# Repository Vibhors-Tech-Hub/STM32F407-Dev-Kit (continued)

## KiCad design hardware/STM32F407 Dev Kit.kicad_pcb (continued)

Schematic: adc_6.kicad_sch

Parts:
C28, C29, C30: 100n; C_0805_2012Metric_Pad1.18x1.45mm_HandSolder
C31, C32, C33: 10n; C_0805_2012Metric_Pad1.18x1.45mm_HandSolder
FB2: ILHB0805ER102VHC41; C_0805_2012Metric_Pad1.18x1.45mm_HandSolder
J5: Conn_01x04; PinHeader_1x04_P2.54mm_Vertical
R17: 10K; R_0805_2012Metric_Pad1.20x1.40mm_HandSolder
R18, R19: 1K; R_0805_2012Metric_Pad1.20x1.40mm_HandSolder
U5: ADS122C04IPW; TSSOP-16_4.4x5mm_P0.65mm

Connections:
+3V3: C28.1, C33.1, FB2.2, J5.1, R17.1, U5.13 (DVDD); also elsewhere on the board
/[6] - ADC/AIN1: C30.2, C31.1, R19.1, U5.10 (AIN1)
/[6] - ADC/AIN2: C30.1, C32.1, R18.1, U5.7 (AIN2)
/[6] - ADC/SENSOR_PIN1: J5.3, R19.2
/[6] - ADC/SENSOR_PIN2: J5.2, R18.2
ADC_DRDY: U5.14 (DRDY); also elsewhere on the board
ADC_RST: R17.2, U5.3 (RESET); also elsewhere on the board
GND: C28.2, C29.2, C31.2, C32.2, C33.2, J5.4, U5.1 (A0), U5.2 (A1), U5.4 (DGND), U5.5 (AVSS); also elsewhere on the board
unnamed: C29.1, FB2.1, U5.12 (AVDD)
SCL: U5.16 (SCL); also elsewhere on the board
SDA: U5.15 (SDA); also elsewhere on the board

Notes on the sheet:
ADC
Address: 100000
Connector

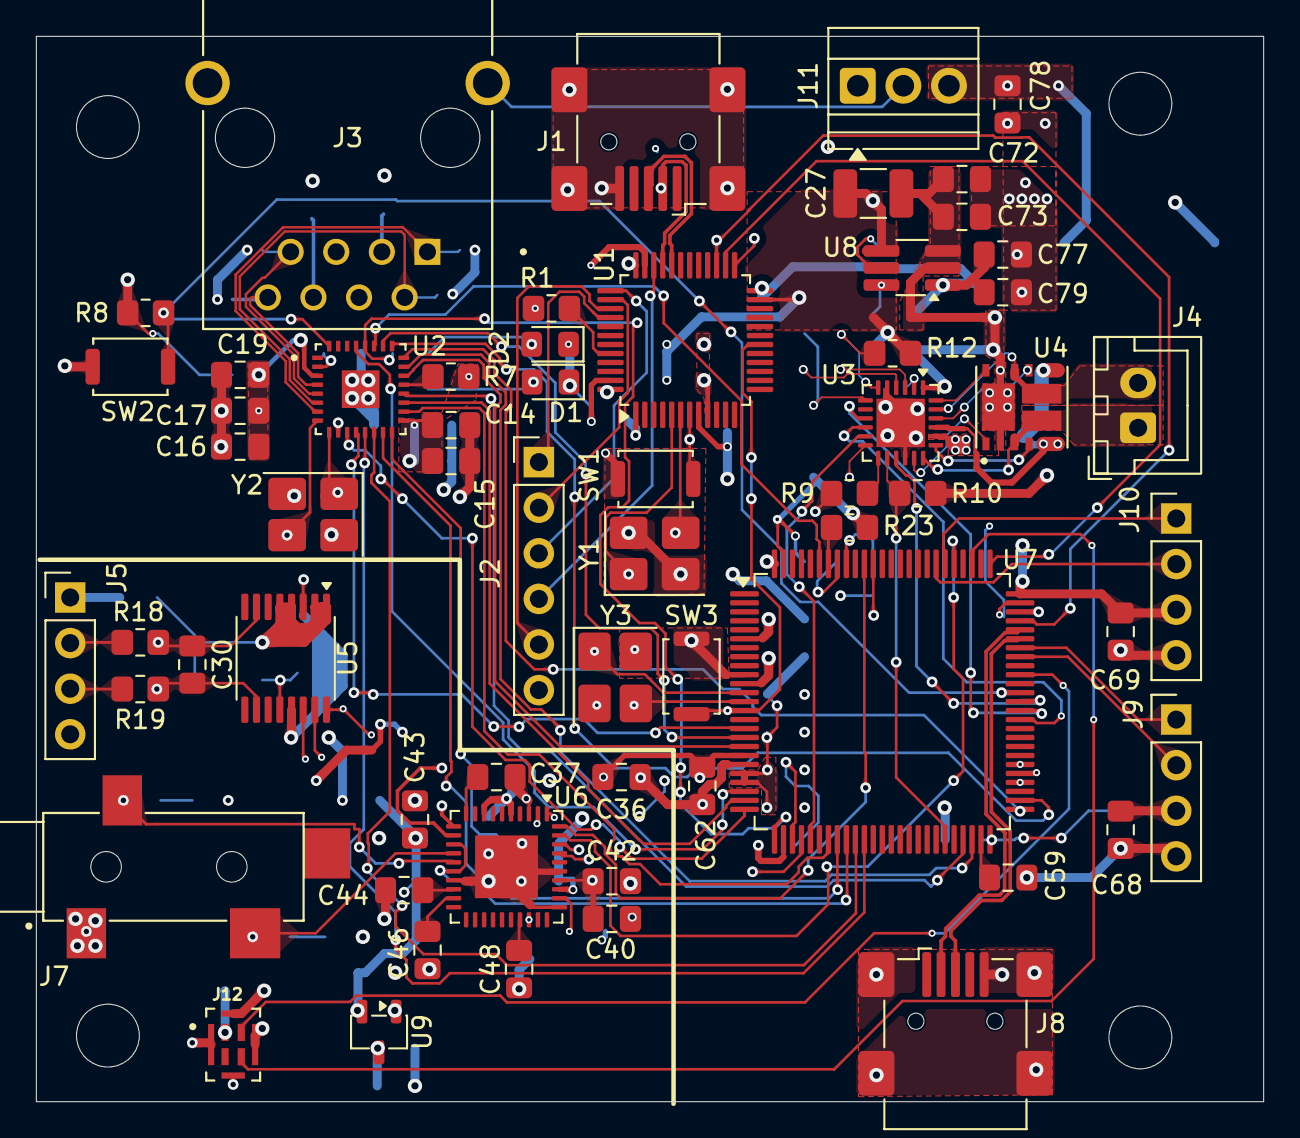
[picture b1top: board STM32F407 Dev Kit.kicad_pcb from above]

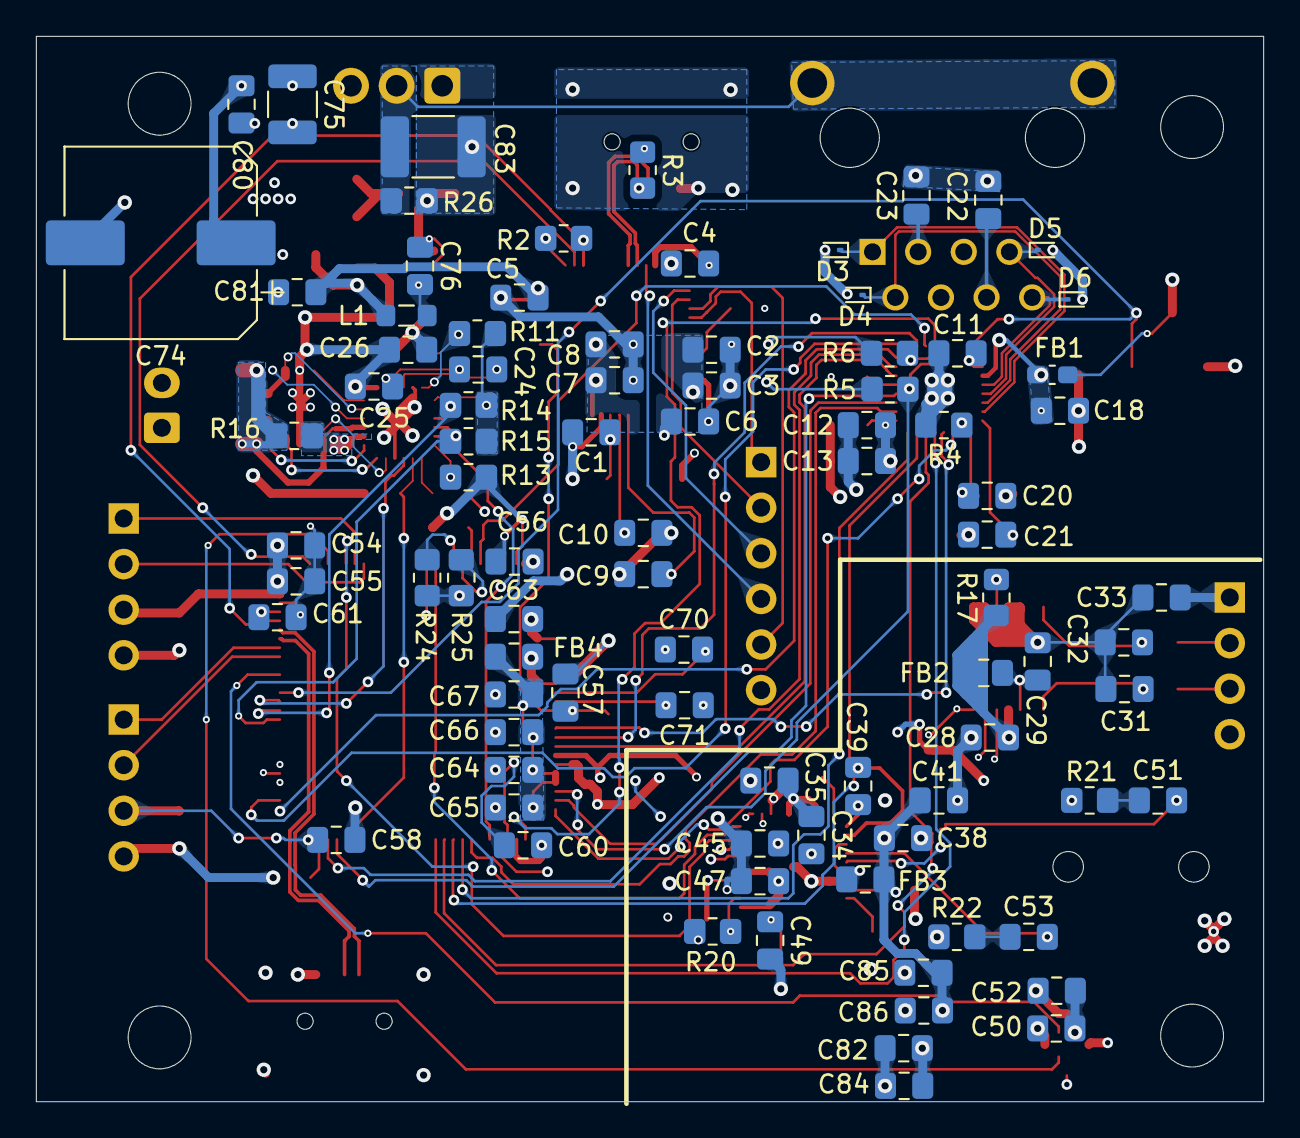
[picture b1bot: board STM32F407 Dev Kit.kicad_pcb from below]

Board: 4 copper layers, 68.4 x 59.3 mm, 153 parts (88 on the bottom side), 113 nets.

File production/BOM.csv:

Reference Designators (RefDes),Footprint,Quantity (Qty),Description,Manufacturer Part Number (MPN)
"C1, C3, C5, C6, C14, C18, C22, C23, C24, C26, C28, C29, C30, C34, C35, C38, C40, C41, C43, C45, C50, C55, C56, C57, C58, C60, C62, C63, C65, C67, C68, C69, C73, C76, C80, C81, C84, C85",0805,38,100n,
"C2, C54",0805,2,4.7u,
C4,0805,1,100nn,
"C7, C15, C19, C31, C32, C33",0805,6,10n,
"C8, C13, C17, C25, C37, C39, C42, C44, C47, C52, C64, C66",0805,12,1u,
"C9, C10, C20, C21, C70, C71",0805,6,22p,
C11,0805,1,2n,
"C12, C16, C36, C46, C72, C82, C86",0805,7,10u,
"C27, C75",0805,2,100u,
"C48, C49",0805,2,150p,
"C51, C53",0805,2,22n,
"C59, C61",0805,2,2.2u,
C74,0805,1,1000u,
"C77, C79",0805,2,22u,
C78,0805,1,47u,
C83,1812,1,10n 2kV,1812B103K202MK
"D1, D2",0805,2,RED,LS R976-NR-1-0-20-R18
"D3, D4, D5, D6",D_SOD-923,4,ESD3V3D9-TP,ESD3V3D9-TP
FB1,0603,1,MPZ1608S331A,MPZ1608S331A
"FB2, FB3, FB4",0805,3,ILHB0805ER102VHC41,ILHB0805ER102VHC41
"J1, J8",USB_Mini-B_Wuerth_65100516121_Horizontal,2,GMSB0531112YEU,GMSB0531112YEU
J2,PinHeader_1x06_P2.54mm_Vertical,1,Conn_01x06,PR20206VBNN
J3,RJMG1S8008101BR,1,RJMG1S8008101BR,RJMG1S8008101BR
J4,JST_XH_B2B-XH-A_1x02_P2.50mm_Vertical,1,B2B-XH-A(LF)(SN),B2B-XH-A(LF)(SN)
"J5, J9, J10",PinHeader_1x04_P2.54mm_Vertical,3,Conn_01x04,PR20204VBNN
J7,SJ-3524-SMT,1,SJ-3524-SMT,SJ-3524-SMT
J11,TBC 2.54mm,1,TBC 2.54mm 10A,397730003
J12,IMP34DT06JTR,1,IMP34DT05,IMP34DT06
L1,0805,1,4.7u,
"R1, R7, R8, R9, R10, R14, R15, R23",0805,8,10k,
R2,0805,1,100r,
R3,0805,1,1.5k,
R4,0805,1,6.49k 1%,
"R5, R6",0805,2,3k3,
"R11, R24, R25",0805,3,2k,
R12,0805,1,3.3k,
R13,0805,1,33k,
R16,0805,1,50m,
R17,0805,1,10K,
"R18, R19",0805,2,1K,
R20,0805,1,1k,
"R21, R22",0805,2,51.1R,
R26,0805,1,1M,
"SW1, SW2, SW3",SW Push SPST NO Alps SKRK,3,SW TACT-SPST,
U1,LQFP-48_7x7mm_P0.5mm,1,STM32F103CBT6,STM32F103CBT7
U2,DP83826IRHBR,1,DP83826IRHBR,DP83826IRHBR
U3,QFN-24-1EP_4x4mm_P0.5mm_EP2.7x2.7mm,1,DRV8701ERGET,DRV8701ERGET
U4,V-DFN5045-12,1,DMHT6016LFJ-13,DMHT6016LFJ-13
U5,TSSOP-16_4.4x5mm_P0.65mm,1,ADS122C04IPW,ADS122C04IPW
U6,VQFN-40-1EP_6x6mm_P0.5mm_EP3.5x3.5mm,1,CS43L22,CS43L22
U7,LQFP-100_14x14mm_P0.5mm,1,STM32F407VGT6,STM32F407VGT6
U8,TSOT-23-6_HandSoldering,1,AP63203WU,AP63203WU
U9,SOT-23-3,1,XC6206P182MR,XC6206P182MR
"Y1, Y3",3225,2,ABM8G-8.000MHZ-18-D2Y-T,ABM8G-8.000MHZ-18-D2Y-T
Y2,3225,1,ABM8G-25.000MHZ-9-B4Y-T,ABM8G-25.000MHZ-9-B4Y-T
